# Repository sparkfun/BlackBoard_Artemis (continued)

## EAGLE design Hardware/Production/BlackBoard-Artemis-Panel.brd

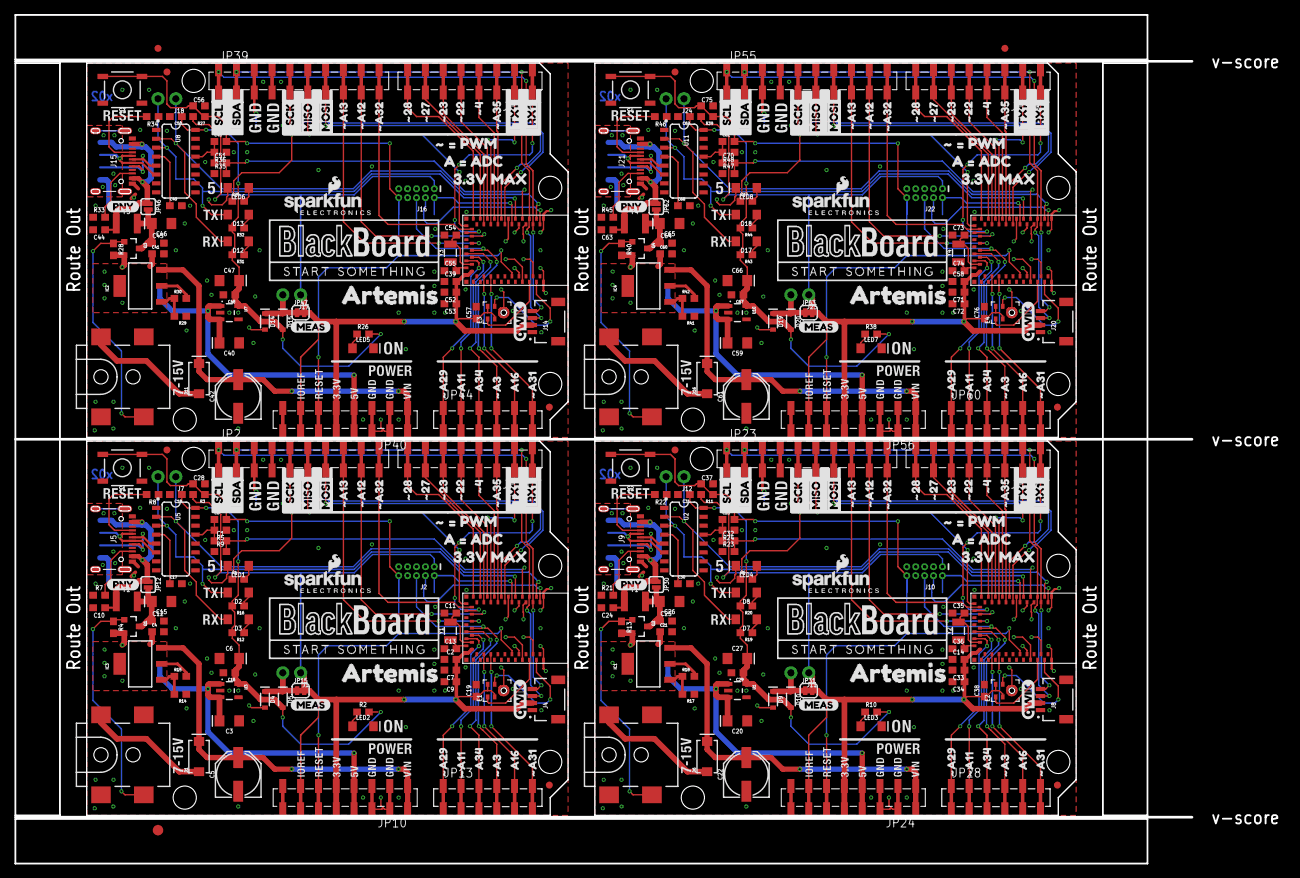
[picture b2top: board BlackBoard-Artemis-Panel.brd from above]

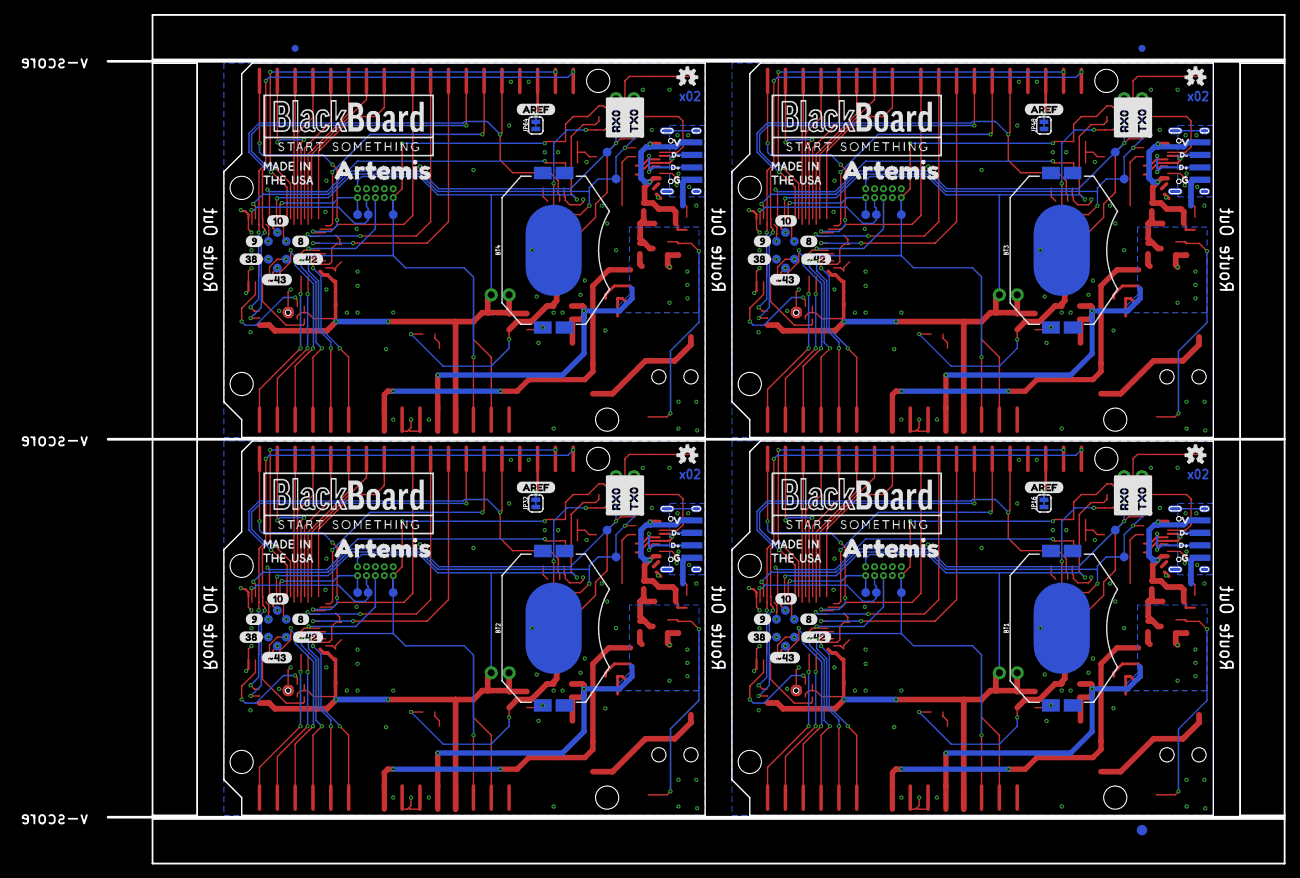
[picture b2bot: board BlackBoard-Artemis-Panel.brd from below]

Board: 2 copper layers, 180.8 x 120.8 mm, 522 parts (131 on the bottom side), 248 nets.

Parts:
BT1, BT2, BT3, BT4: CR2032; BATTCON_20MM_4LEGS_OVERPASTE
C1, C32, C51, C70: 2.2uF; 0603
C2, C4, C8, C10, C12, C14, C18, C19, C21, C23, C24, C25, C31, C38, C39, C41, C43, C44, C45, C50, C57, C58, C60, C62, C63, C64, C69, C76: 0.1uF; 0603
C3, C6, C15, C20, C26, C27, C40, C46, C47, C59, C65, C66: 10uF; EIA3216
C5, C22, C42, C61: 47uF; PANASONIC_D
C7, C33, C52, C71: 10uF; 0603
C9, C16, C29, C34, C48, C53, C67, C72: 1.0uF; 0603
C11, C13, C35, C36, C54, C55, C73, C74: 15pF; 0603
C17, C30, C49, C68: 10nF; 0603
C28, C37, C56, C75: 1nF; 0603
D1, D6, D11, D16: 1A/40V/500mV; SMA-DIODE
D2, D8, D13, D18: GREEN; LED-1206
D3, D7, D12, D17: Yellow; LED-1206
D4, D5, D9, D10, D14, D15, D19, D20: 1A/23V/620mV; SOD-323
E1, E2, E3, E4: SPH0641LM4H-1; SPH0641LM4H-1_MICROPHONE
E$1, E$2, E$3, E$4: FIDUCIAL-1X2
E$5, E$6: FIDUCIAL-1.5X3
F1, F2, F3, F4: 6V/2A; 1210
FRAME1, FRAME2, FRAME3, FRAME4: FRAME-LETTERNO_PACKAGE; DUMMY
IC1, IC2, IC3, IC4: LM1117; SOT223-ALT1
J1, J7, J11, J12, J17, J18, J23, J24: 1X02_NO_SILK
J2, J10, J16, J22: CORTEX_DEBUG; 2X5-PTH-1.27MM-NO_SILK
J3, J6, J13, J19: POWER_JACKTOE; POWER_JACK_SMD_OVERPASTE_TOE
J4, J8, J14, J20: JST04_1MM_RA
J5, J9, J15, J21: USB-C; USB-C-16P
JP1, JP25, JP41, JP57: SFE_LOGO_NAME.1_INCH; SFE_LOGO_NAME_.1
JP2, JP23, JP39, JP55: M10SMD_COMBO; 1X10_SMD_COMBINED
JP3, JP4, JP5, JP6, JP17, JP18, JP19, JP20, JP33, JP34, JP35, JP36, JP49, JP50, JP51, JP52: STAND-OFF
JP7, JP26, JP42, JP58: SFE_LOGO_FLAME.1_INCH; SFE_LOGO_FLAME_.1
JP8, JP9, JP21, JP22, JP37, JP38, JP53, JP54: FIDUCIAL1X2; FIDUCIAL-1X2
JP10, JP24, JP40, JP56: 1X08_SMD_COMBINED
JP11, JP27, JP43, JP59: JP11; 1X08_SMD_COMBINED
JP12, JP30, JP46, JP62: SMT-JUMPER_2_NO_SILK
JP13, JP28, JP44, JP60: 1X06_SMD_STRAIGHT_COMBO
JP14, JP29, JP45, JP61: USB_SOLDER_PADS; USB-SOLDER-PADS
JP15, JP16, JP31, JP32, JP47, JP48, JP63, JP64: SMT-JUMPER_2_NC_TRACE_SILK
LED1, LED4, LED6, LED8: BLUE; LED-1206
LED2, LED3, LED5, LED7: GREEN; LED-1206
Q1, Q2, Q3, Q4: 1.1A/60V/600mΩ; SOT23-3
R1, R6, R12, R16, R19, R20, R25, R31, R32, R37, R43, R44: 4.7k; 0603
R2, R4, R9, R10, R13, R23, R26, R28, R35, R38, R40, R47: 10k; 0603
R3, R5, R11, R24, R27, R36, R39, R48: 100k; 0603
R7, R8, R21, R22, R33, R34, R45, R46: 5.1k; 0603
R14, R17, R29, R41: 715; 0603
R15, R18, R30, R42: 240; 0603
S1, S2, S3, S4: TACTILE_SWITCH_SMD_5.2MM
TP1, TP2, TP3, TP4, TP7, TP8, TP9, TP11, TP12, TP13, TP14, TP16, TP17, TP18, TP19, TP20, TP21, TP22, TP23, TP24, TP27, TP28, TP29, TP30, TP31, TP32, TP33, TP34, TP35, TP38, TP39, TP40, TP41, TP42, TP43, TP44: PAD.03X.05
TP5, TP6, TP10, TP15, TP25, TP26, TP36, TP37: TEST-POINT3X5; PAD.03X.05
U1, U3, U7, U10: AP2112-3.3V; SOT23-5
U2, U5, U8, U11: CH340C; SO016
U4, U6, U9, U12: ARTEMIS_MODULESMD; ARTEMIS_FP
U$1, U$3, U$6, U$7, U$96, U$97, U$143, U$144: BLACKBOARDLOGO#PNG
U$2, U$37, U$102, U$149: D#3
U$4, U$8, U$98, U$145: MADEINUSA#PNG
U$5, U$16, U$95, U$142: OSHW-LOGOS; OSHW-LOGO-S
U$9, U$23, U$99, U$146: QWIIC_COPYRIGHT_SMALL
U$10, U$39, U$103, U$150: D#4
U$11, U$24, U$100, U$147: G1
U$12, U$32, U$101, U$148: V0
U$13, U$40, U$104, U$151: PNY0
U$14, U$15, U$41, U$42, U$105, U$106, U$152, U$153: ARTEMIS0
U$17, U$43, U$107, U$154: A160
U$18, U$93, U$140, U$187: SCL1
U$19, U$44, U$108, U$155: #48
U$20, U$92, U$139, U$186: AREF2
U$21, U$45, U$109, U$156: #229
U$22, U$94, U$141, U$188: SDA0
U$25, U$46, U$110, U$157: #2310
U$26, U$51, U$111, U$158: #2711
U$27, U$52, U$112, U$159: #2812
U$28, U$54, U$113, U$160: #A31
U$29, U$55, U$114, U$161: #A113
U$30, U$56, U$115, U$162: #A294
U$31, U$57, U$116, U$163: #A310
U$33, U$58, U$117, U$164: #A357
U$34, U$59, U$118, U$165: #A1214
U$35, U$68, U$119, U$166: #A1315
U$36, U$73, U$120, U$167: #A3213
U$38, U$74, U$121, U$168: A342
U$47, U$75, U$122, U$169: MISO8
U$48, U$76, U$123, U$170: MOSI7
U$49, U$90, U$137, U$184: RX01
U$50, U$77, U$124, U$171: SCK9
U$53, U$91, U$138, U$185: TX00
U$60, U$78, U$125, U$172: #425
U$61, U$79, U$126, U$173: #434
U$62, U$80, U$127, U$174: 80
U$63, U$81, U$128, U$175: 91
U$64, U$82, U$129, U$176: 102
U$65, U$83, U$130, U$177: 383
U$66, U$84, U$131, U$178: #_#_PWM7
U$67, U$85, U$132, U$179: 3#3V_MAX2
U$69, U$86, U$133, U$180: A_#_ADC6
U$70, U$87, U$134, U$181: MEAS3
U$71, U$88, U$135, U$182: RX11
U$72, U$89, U$136, U$183: TX10
Y1, Y2, Y3, Y4: 32.768kHz; CRYSTAL-SMD-3.2X1.5MM

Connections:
3.3V: C6.+, C16.1, C18.1, D5.A, R2.2, R12.2, R16.2, U3.5, U5.16
3.3V1: C27.+, C29.1, C31.1, D10.A, R10.2, R19.2, R20.2, U1.5, U2.16
3.3V2: C47.+, C48.1, C50.1, D15.A, R26.2, R31.2, R32.2, U7.5, U8.16
3.3V3: C66.+, C67.1, C69.1, D20.A, R38.2, R43.2, R44.2, U10.5, U11.16
5V: C3.+, C4.1, IC3.2, IC3.4, JP10.4A, JP10.4B, Q1.2, R4.2, R15.2, U3.1, U3.3
5V1: C20.+, C21.1, IC1.2, IC1.4, JP24.4A, JP24.4B, Q2.2, R13.2, R18.2, U1.1, U1.3
5V2: C40.+, C41.1, IC2.2, IC2.4, JP40.4A, JP40.4B, Q3.2, R28.2, R30.2, U7.1, U7.3
5V3: C59.+, C60.1, IC4.2, IC4.4, JP56.4A, JP56.4B, Q4.2, R40.2, R42.2, U10.1, U10.3
!DTR: C1.1, C8.1, R5.2, U5.13
!DTR1: C23.1, C32.1, R24.2, U2.13
!DTR2: C43.1, C51.1, R36.2, U8.13
!DTR3: C62.1, C70.1, R48.2, U11.13
!RESET: C8.2, C28.1, J2.10, JP10.6A, JP10.6B, R3.1, S1.3, S1.4, TP3.P$1, U4.~RST
!RESET1: C23.2, C37.1, J10.10, JP24.6A, JP24.6B, R11.1, S2.3, S2.4, TP16.P$1, U6.~RST
!RESET2: C43.2, C56.1, J16.10, JP40.6A, JP40.6B, R27.1, S3.3, S3.4, TP27.P$1, U9.~RST
!RESET3: C62.2, C75.1, J22.10, JP56.6A, JP56.6B, R39.1, S4.3, S4.4, TP38.P$1, U12.~RST
AD1: JP28.5A, JP28.5B, U6.AD16
AD2: JP28.3A, JP28.3B, U6.AD34
AD3: JP44.5A, JP44.5B, U9.AD16
AD4: JP44.3A, JP44.3B, U9.AD34
AD5: JP60.5A, JP60.5B, U12.AD16
AD6: JP60.3A, JP60.3B, U12.AD34
AD16: JP13.5A, JP13.5B, U4.AD16
AD34: JP13.3A, JP13.3B, U4.AD34
BOOT: C1.2, R9.2, U4.BOOT
BOOT1: C32.2, R23.2, U6.BOOT
BOOT2: C51.2, R35.2, U9.BOOT
BOOT3: C70.2, R47.2, U12.BOOT
CC1: J5.A5, R8.2
CC2: J5.B5, R7.2
CC3: J9.B5, R21.2
CC4: J9.A5, R22.2
CC5: J15.B5, R33.2
CC6: J15.A5, R34.2
CC7: J21.B5, R45.2
CC8: J21.A5, R46.2
D1: TP20.P$1, U6.D8
D2: TP21.P$1, U6.D9
D3: TP22.P$1, U6.D10
D4: TP19.P$1, U6.D38
D5: TP31.P$1, U9.D8
D6: TP32.P$1, U9.D9
D7: TP33.P$1, U9.D10
D7/MOSI: JP2.7A, JP2.7B, U4.D7
D7/MOSI1: JP23.7A, JP23.7B, U6.D7
D7/MOSI2: JP39.7A, JP39.7B, U9.D7
D7/MOSI3: JP55.7A, JP55.7B, U12.D7
D8: TP12.P$1, U4.D8
D9: TP13.P$1, U4.D9
D10: TP14.P$1, U4.D10
D11: TP30.P$1, U9.D38
D12: TP42.P$1, U12.D8
D13: TP43.P$1, U12.D9
D14: TP44.P$1, U12.D10
D15: TP41.P$1, U12.D38
D38: TP11.P$1, U4.D38
D40/SDA: J4.3, JP2.2A, JP2.2B, U4.D40
D40/SDA1: J8.3, JP23.2A, JP23.2B, U6.D40
D40/SDA2: J14.3, JP39.2A, JP39.2B, U9.D40
D40/SDA3: J20.3, JP55.2A, JP55.2B, U12.D40
D+: J5.A6, J5.B6, JP14.D+, U5.5
D+1: J9.A6, J9.B6, JP29.D+, U2.5
D+2: J15.A6, J15.B6, JP45.D+, U8.5
D+3: J21.A6, J21.B6, JP61.D+, U11.5
D-: J5.A7, J5.B7, JP14.D-, U5.6
D-1: J9.A7, J9.B7, JP29.D-, U2.6
D-2: J15.A7, J15.B7, JP45.D-, U8.6
D-3: J21.A7, J21.B7, JP61.D-, U11.6
GND: BT1.2, C2.1, C3.-, C4.2, C5.-, C6.-, C7.2, C9.2, C10.2, C11.1, C12.2, C13.1, C15.-, C16.2, C17.2, C18.2, C19.2, C28.2, E1.3, E1.6, E1.7, E1.8, J2.3, J2.5, J2.9, J3.GND, J4.1, J5.GND, J5.GND2, JP2.4A, JP2.4B, JP10.2A, JP10.2B, JP10.3A, JP10.3B, JP14.GND, JP16.1, LED1.C, LED2.C, R5.1, R7.1, R8.1, R9.1, R14.1, S1.1, S1.2, U3.2, U4.GND@1, U4.GND@22, U4.GND@38, U4.GND@39, U4.GND@47, U4.GND@59, U5.1
GND1: BT2.2, C14.1, C20.-, C21.2, C22.-, C24.2, C25.2, C26.-, C27.-, C29.2, C30.2, C31.2, C33.2, C34.2, C35.1, C36.1, C37.2, C38.2, E2.3, E2.6, E2.7, E2.8, J6.GND, J8.1, J9.GND, J9.GND2, J10.3, J10.5, J10.9, JP23.4A, JP23.4B, JP24.2A, JP24.2B, JP24.3A, JP24.3B, JP29.GND, JP32.1, LED3.C, LED4.C, R17.1, R21.1, R22.1, R23.1, R24.1, S2.1, S2.2, U1.2, U2.1, U6.GND@1, U6.GND@22, U6.GND@38, U6.GND@39, U6.GND@47, U6.GND@59
GND2: BT3.2, C39.1, C40.-, C41.2, C42.-, C44.2, C45.2, C46.-, C47.-, C48.2, C49.2, C50.2, C52.2, C53.2, C54.1, C55.1, C56.2, C57.2, E3.3, E3.6, E3.7, E3.8, J13.GND, J14.1, J15.GND, J15.GND2, J16.3, J16.5, J16.9, JP39.4A, JP39.4B, JP40.2A, JP40.2B, JP40.3A, JP40.3B, JP45.GND, JP48.1, LED5.C, LED6.C, R29.1, R33.1, R34.1, R35.1, R36.1, S3.1, S3.2, U7.2, U8.1, U9.GND@1, U9.GND@22, U9.GND@38, U9.GND@39, U9.GND@47, U9.GND@59
GND3: BT4.2, C58.1, C59.-, C60.2, C61.-, C63.2, C64.2, C65.-, C66.-, C67.2, C68.2, C69.2, C71.2, C72.2, C73.1, C74.1, C75.2, C76.2, E4.3, E4.6, E4.7, E4.8, J19.GND, J20.1, J21.GND, J21.GND2, J22.3, J22.5, J22.9, JP55.4A, JP55.4B, JP56.2A, JP56.2B, JP56.3A, JP56.3B, JP61.GND, JP64.1, LED7.C, LED8.C, R41.1, R45.1, R46.1, R47.1, R48.1, S4.1, S4.2, U10.2, U11.1, U12.GND@1, U12.GND@22, U12.GND@38, U12.GND@39, U12.GND@47, U12.GND@59
INSERT: J3.P$4, Q1.1, R4.1
INSERT1: J6.P$4, Q2.1, R13.1
INSERT2: J13.P$4, Q3.1, R28.1
INSERT3: J19.P$4, Q4.1, R40.1
unnamed: LED1.A, R1.2
unnamed: LED2.A, R2.1
unnamed: D4.C, D5.C, J1.2, JP15.1
unnamed: D2.A, R16.1
unnamed: C17.1, U5.4
unnamed: C11.2, U4.XO, Y1.P$2
unnamed: C13.2, U4.XI, Y1.P$1
unnamed: D3.A, R12.1
unnamed: JP2.3A, JP2.3B, JP16.2
unnamed: LED3.A, R10.1
unnamed: LED4.A, R6.2
unnamed: IC1.1, R17.2, R18.1
unnamed: D8.A, R20.1
unnamed: IC3.1, R14.2, R15.1
unnamed: D7.A, R19.1
unnamed: C30.1, U2.4
unnamed: D9.C, D10.C, J11.2, JP31.1
unnamed: C35.2, U6.XO, Y2.P$2
unnamed: C36.2, U6.XI, Y2.P$1
unnamed: JP23.3A, JP23.3B, JP32.2
unnamed: LED5.A, R26.1
unnamed: LED6.A, R25.2
unnamed: IC2.1, R29.2, R30.1
unnamed: D13.A, R32.1
unnamed: D12.A, R31.1
unnamed: C49.1, U8.4
unnamed: D14.C, D15.C, J17.2, JP47.1
unnamed: C54.2, U9.XO, Y3.P$2
unnamed: C55.2, U9.XI, Y3.P$1
unnamed: JP39.3A, JP39.3B, JP48.2
unnamed: LED7.A, R38.1
unnamed: LED8.A, R37.2
unnamed: IC4.1, R41.2, R42.1
unnamed: D18.A, R44.1
unnamed: D17.A, R43.1
unnamed: C68.1, U11.4
unnamed: D19.C, D20.C, J23.2, JP63.1
unnamed: C73.2, U12.XO, Y4.P$2
unnamed: C74.2, U12.XI, Y4.P$1
unnamed: JP55.3A, JP55.3B, JP64.2
PDMCLK: E1.4, U4.~D37
PDMCLK1: E2.4, U6.~D37
PDMCLK2: E3.4, U9.~D37
PDMCLK3: E4.4, U12.~D37
PDMDATA: E1.1, U4.D36
PDMDATA1: E2.1, U6.D36
PDMDATA2: E3.1, U9.D36
PDMDATA3: E4.1, U12.D36
PWRIN: D1.A, J3.VIN0
PWRIN1: D6.A, J6.VIN0
PWRIN2: D11.A, J13.VIN0
PWRIN3: D16.A, J19.VIN0
RXI-0: D3.C, J7.1, TP5.P$1, U4.RXI-0, U5.2
RXI-1: D7.C, J12.1, TP10.P$1, U2.2, U6.RXI-0
RXI-2: D12.C, J18.1, TP25.P$1, U8.2, U9.RXI-0
RXI-3: D17.C, J24.1, TP36.P$1, U11.2, U12.RXI-0
SHLD: J5.SHLD1, J5.SHLD2, J5.SHLD3, J5.SHLD4, J5.SHLD5, J5.SHLD6, J5.SHLD7, J5.SHLD8
SHLD1: J9.SHLD1, J9.SHLD2, J9.SHLD3, J9.SHLD4, J9.SHLD5, J9.SHLD6, J9.SHLD7, J9.SHLD8
SHLD2: J15.SHLD1, J15.SHLD2, J15.SHLD3, J15.SHLD4, J15.SHLD5, J15.SHLD6, J15.SHLD7, J15.SHLD8
SHLD3: J21.SHLD1, J21.SHLD2, J21.SHLD3, J21.SHLD4, J21.SHLD5, J21.SHLD6, J21.SHLD7, J21.SHLD8
SWDCK: J2.4, TP1.P$1, U4.SWDCK
SWDCK1: J10.4, TP4.P$1, U6.SWDCK
SWDCK2: J16.4, TP23.P$1, U9.SWDCK
SWDCK3: J22.4, TP34.P$1, U12.SWDCK
SWDIO: J2.2, TP2.P$1, U4.SWDIO
SWDIO1: J10.2, TP7.P$1, U6.SWDIO
SWDIO2: J16.2, TP24.P$1, U9.SWDIO
SWDIO3: J22.2, TP35.P$1, U12.SWDIO
TXO-0: D2.C, J7.2, TP6.P$1, U4.TXO-0, U5.3
TXO-1: D8.C, J12.2, TP15.P$1, U2.3, U6.TXO-0
TXO-2: D13.C, J18.2, TP26.P$1, U8.3, U9.TXO-0
TXO-3: D18.C, J24.2, TP37.P$1, U11.3, U12.TXO-0
USBVCC: C12.1, C15.+, F2.2, JP12.2, Q1.3
USBVCC1: C25.1, C26.+, F1.2, JP30.2, Q2.3
USBVCC2: C45.1, C46.+, F3.2, JP46.2, Q3.3
USBVCC3: C64.1, C65.+, F4.2, JP62.2, Q4.3
VDD: C2.2, C7.1, C9.1, C19.1, E1.2, E1.5, J1.1, J2.1, J4.2, JP10.5A, JP10.5B, JP10.7A, JP10.7B, JP15.2, R3.2, U4.VDD@36, U4.VDD@37
VDD1: C14.2, C33.1, C34.1, C38.1, E2.2, E2.5, J8.2, J10.1, J11.1, JP24.5A, JP24.5B, JP24.7A, JP24.7B, JP31.2, R11.2, U6.VDD@36, U6.VDD@37
VDD2: C39.2, C52.1, C53.1, C57.1, E3.2, E3.5, J14.2, J16.1, J17.1, JP40.5A, JP40.5B, JP40.7A, JP40.7B, JP47.2, R27.2, U9.VDD@36, U9.VDD@37
VDD3: C58.2, C71.1, C72.1, C76.1, E4.2, E4.5, J20.2, J22.1, J23.1, JP56.5A, JP56.5B, JP56.7A, JP56.7B, JP63.2, R39.2, U12.VDD@36, U12.VDD@37
VIN: C5.+, D1.C, IC3.3, JP10.1A, JP10.1B
VIN1: C22.+, D6.C, IC1.3, JP24.1A, JP24.1B
VIN2: C42.+, D11.C, IC2.3, JP40.1A, JP40.1B
VIN3: C61.+, D16.C, IC4.3, JP56.1A, JP56.1B
VUSB: C10.1, F2.1, J5.VBUS1, J5.VBUS2, JP12.1, JP14.VBUS
VUSB1: C24.1, F1.1, J9.VBUS1, J9.VBUS2, JP29.VBUS, JP30.1
VUSB2: C44.1, F3.1, J15.VBUS1, J15.VBUS2, JP45.VBUS, JP46.1
VUSB3: C63.1, F4.1, J21.VBUS1, J21.VBUS2, JP61.VBUS, JP62.1
V_BATT: BT1.1, D4.A
V_BATT1: BT2.1, D9.A
V_BATT2: BT3.1, D14.A
V_BATT3: BT4.1, D19.A
~AD1: JP28.6A, JP28.6B, U6.~AD31
~AD2: JP28.1A, JP28.1B, U6.~AD29
~AD3: JP28.2A, JP28.2B, U6.~AD11
~AD3/SWO: J2.6, JP13.4A, JP13.4B, U4.~AD33/SWO
~AD3/SWO1: J10.6, JP28.4A, JP28.4B, U6.~AD33/SWO
~AD3/SWO2: J16.6, JP44.4A, JP44.4B, U9.~AD33/SWO
~AD3/SWO3: J22.6, JP60.4A, JP60.4B, U12.~AD33/SWO
~AD4: JP27.3A, JP27.3B, U6.~AD35
~AD5: JP23.10A, JP23.10B, U6.~AD32
~AD6: JP23.9A, JP23.9B, U6.~AD12
~AD7: JP23.8A, JP23.8B, U6.~AD13
~AD8: JP44.6A, JP44.6B, U9.~AD31
~AD9: JP44.1A, JP44.1B, U9.~AD29
~AD10: JP44.2A, JP44.2B, U9.~AD11
~AD11: JP13.2A, JP13.2B, U4.~AD11
~AD12: JP2.9A, JP2.9B, U4.~AD12
~AD13: JP2.8A, JP2.8B, U4.~AD13
~AD14: JP43.3A, JP43.3B, U9.~AD35
~AD15: JP39.10A, JP39.10B, U9.~AD32
~AD16: JP39.9A, JP39.9B, U9.~AD12
~AD17: JP39.8A, JP39.8B, U9.~AD13
~AD18: JP60.6A, JP60.6B, U12.~AD31
~AD19: JP60.1A, JP60.1B, U12.~AD29
~AD20: JP60.2A, JP60.2B, U12.~AD11
~AD21: JP59.3A, JP59.3B, U12.~AD35
~AD22: JP55.10A, JP55.10B, U12.~AD32
~AD23: JP55.9A, JP55.9B, U12.~AD12
~AD24: JP55.8A, JP55.8B, U12.~AD13
~AD29: JP13.1A, JP13.1B, U4.~AD29
~AD31: JP13.6A, JP13.6B, U4.~AD31
~AD32: JP2.10A, JP2.10B, U4.~AD32
~AD35: JP11.3A, JP11.3B, U4.~AD35
~D1: JP27.4A, JP27.4B, U6.~D4
~D2: JP27.5A, JP27.5B, U6.~D22
~D3: JP27.6A, JP27.6B, U6.~D23
~D4: JP11.4A, JP11.4B, U4.~D4
~D5: JP27.7A, JP27.7B, U6.~D27
~D5/SCK: JP2.5A, JP2.5B, R1.1, U4.~D5
~D5/SCK1: JP23.5A, JP23.5B, R6.1, U6.~D5
~D5/SCK2: JP39.5A, JP39.5B, R25.1, U9.~D5
~D5/SCK3: JP55.5A, JP55.5B, R37.1, U12.~D5
~D6: JP27.8A, JP27.8B, U6.~D28
~D6/MISO: JP2.6A, JP2.6B, U4.~D6
~D6/MISO1: JP23.6A, JP23.6B, U6.~D6
~D6/MISO2: JP39.6A, JP39.6B, U9.~D6
~D6/MISO3: JP55.6A, JP55.6B, U12.~D6
~D7: TP18.P$1, U6.~D42
~D8: TP17.P$1, U6.~D43
~D9: JP43.4A, JP43.4B, U9.~D4
~D10: JP43.5A, JP43.5B, U9.~D22
~D11: JP43.6A, JP43.6B, U9.~D23
~D12: JP43.7A, JP43.7B, U9.~D27
~D13: JP43.8A, JP43.8B, U9.~D28
~D14: TP29.P$1, U9.~D42
~D15: TP28.P$1, U9.~D43
~D16: JP59.4A, JP59.4B, U12.~D4
~D17: JP59.5A, JP59.5B, U12.~D22
~D18: JP59.6A, JP59.6B, U12.~D23
~D19: JP59.7A, JP59.7B, U12.~D27
~D20: JP59.8A, JP59.8B, U12.~D28
~D21: TP40.P$1, U12.~D42
~D22: JP11.5A, JP11.5B, U4.~D22
~D23: JP11.6A, JP11.6B, U4.~D23
~D24: TP39.P$1, U12.~D43
~D24/TXO-1: JP11.2A, JP11.2B, U4.~D24
~D24/TXO-2: JP27.2A, JP27.2B, U6.~D24
~D24/TXO-3: JP43.2A, JP43.2B, U9.~D24
~D24/TXO-4: JP59.2A, JP59.2B, U12.~D24
~D25/RXI-1: JP11.1A, JP11.1B, U4.~D25
~D25/RXI-2: JP27.1A, JP27.1B, U6.~D25
~D25/RXI-3: JP43.1A, JP43.1B, U9.~D25
~D25/RXI-4: JP59.1A, JP59.1B, U12.~D25
~D27: JP11.7A, JP11.7B, U4.~D27
~D28: JP11.8A, JP11.8B, U4.~D28
~D39/SCL: J4.4, JP2.1A, JP2.1B, U4.~D39
~D39/SCL1: J8.4, JP23.1A, JP23.1B, U6.~D39
~D39/SCL2: J14.4, JP39.1A, JP39.1B, U9.~D39
~D39/SCL3: J20.4, JP55.1A, JP55.1B, U12.~D39
~D42: TP9.P$1, U4.~D42
~D43: TP8.P$1, U4.~D43

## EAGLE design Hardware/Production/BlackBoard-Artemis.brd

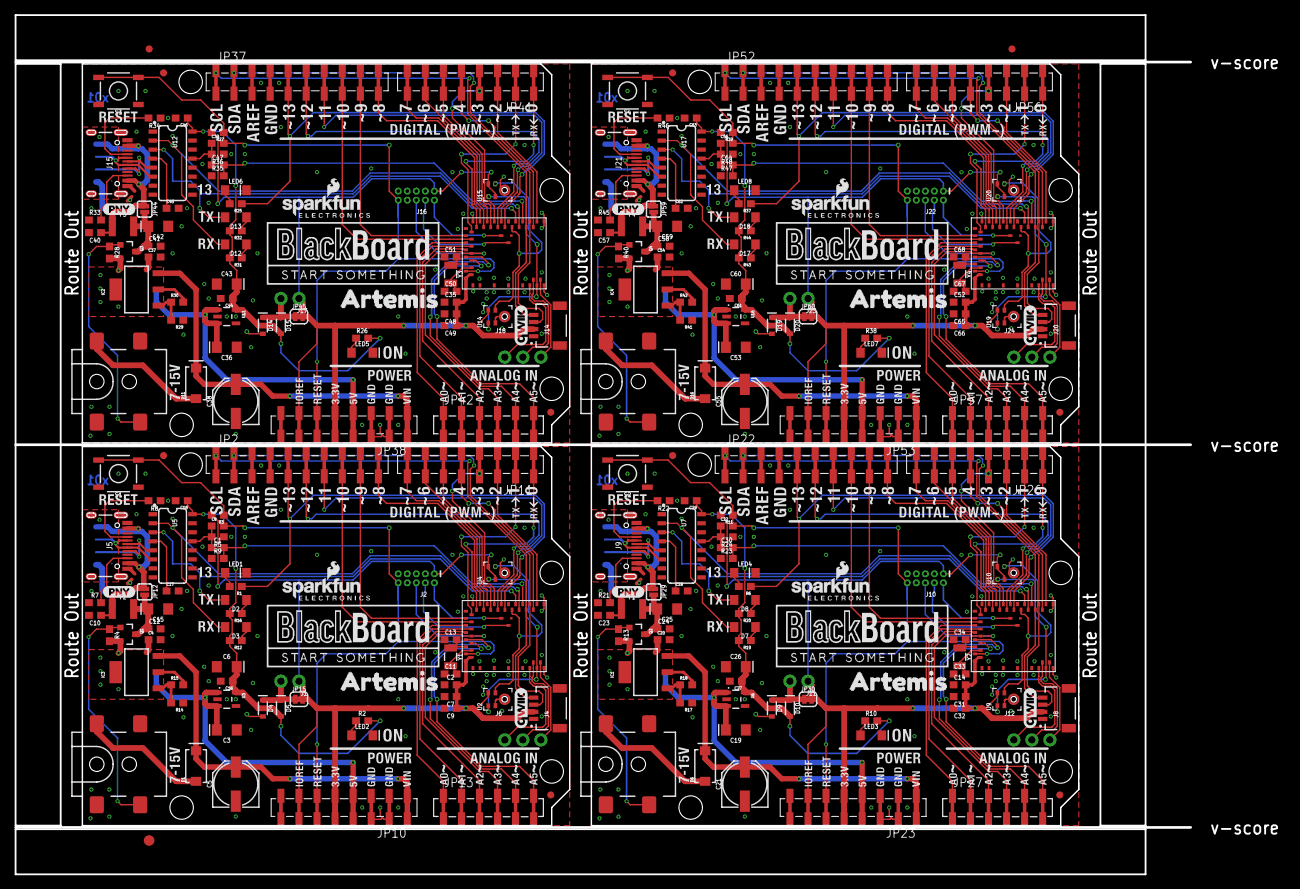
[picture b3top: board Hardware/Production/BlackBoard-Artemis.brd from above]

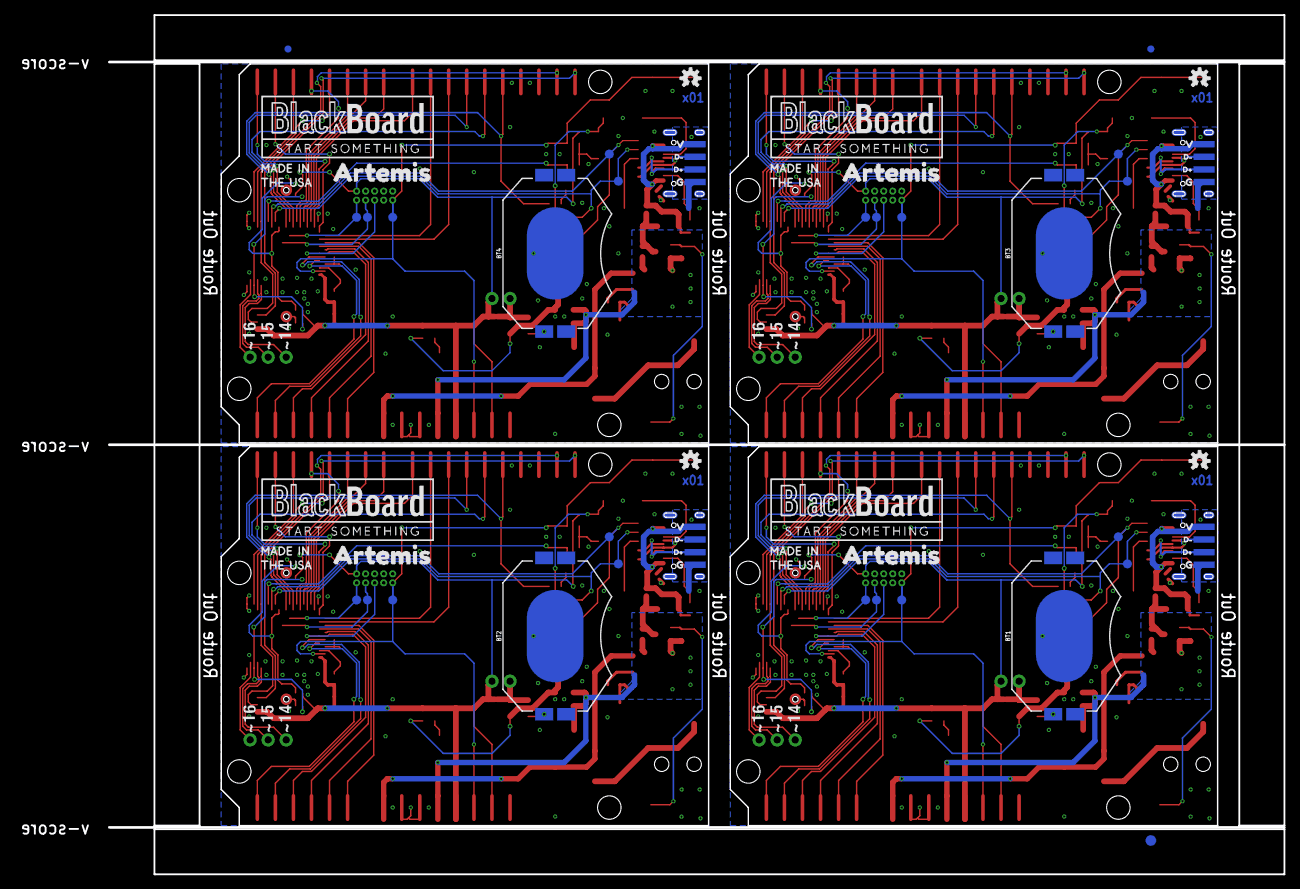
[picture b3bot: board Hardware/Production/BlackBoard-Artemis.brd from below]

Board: 2 copper layers, 178.5 x 120.8 mm, 354 parts (63 on the bottom side), 232 nets.

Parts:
BT1, BT2, BT3, BT4: CR2032; BATTCON_20MM_4LEGS_OVERPASTE
C1, C30, C47, C64: 2.2uF; 0603
C2, C4, C10, C12, C14, C18, C20, C23, C24, C29, C35, C37, C40, C41, C46, C52, C54, C57, C58, C63: 0.1uF; 0603
C3, C6, C15, C19, C25, C26, C36, C42, C43, C53, C59, C60: 10uF; EIA3216
C5, C21, C38, C55: 47uF; PANASONIC_D
C7, C31, C48, C65: 10uF; 0603
C8, C17, C22, C28, C39, C45, C56, C62: 10nF; 0603
C9, C16, C27, C32, C44, C49, C61, C66: 1.0uF; 0603
C11, C13, C33, C34, C50, C51, C67, C68: 15pF; 0603
D1, D6, D11, D16: 1A/40V/500mV; SMA-DIODE
D2, D8, D13, D18: GREEN; LED-1206
D3, D7, D12, D17: Yellow; LED-1206
D4, D5, D9, D10, D14, D15, D19, D20: 1A/23V/620mV; SOD-323
E$1, E$2, E$3, E$4: FIDUCIAL-1X2
E$5, E$6: FIDUCIAL-1.5X3
F1, F2, F3, F4: 6V/2A; 1210
FRAME1, FRAME3, FRAME5, FRAME7: FRAME-LETTER; CREATIVE_COMMONS
FRAME2, FRAME4, FRAME6, FRAME8: FRAME-LETTERNO_PACKAGE; DUMMY
IC1, IC2, IC3, IC4: LM1117; SOT223-ALT1
J1, J11, J17, J23: 1X02_NO_SILK
J2, J10, J16, J22: CORTEX_DEBUG; 2X5-PTH-1.27MM-NO_SILK
J3, J7, J13, J19: POWER_JACKSUPER_BOMB_DIGITY; POWER_JACK_SMD_OVERPASTE_SUPER_BOMB_DIGITY
J4, J8, J14, J20: JST04_1MM_RA
J5, J9, J15, J21: USB C; USB-C-16P
J6, J12, J18, J24: 1X03_NO_SILK
JP1, JP24, JP39, JP54: SFE_LOGO_NAME.1_INCH; SFE_LOGO_NAME_.1
JP2, JP22, JP37, JP52: M10SMD_COMBO; 1X10_SMD_COMBINED
JP3, JP4, JP5, JP6, JP16, JP17, JP18, JP19, JP31, JP32, JP33, JP34, JP46, JP47, JP48, JP49: STAND-OFF
JP7, JP25, JP40, JP55: SFE_LOGO_FLAME.1_INCH; SFE_LOGO_FLAME_.1
JP8, JP9, JP20, JP21, JP35, JP36, JP50, JP51: FIDUCIAL1X2; FIDUCIAL-1X2
JP10, JP23, JP38, JP53: 1X08_SMD_COMBINED
JP11, JP26, JP41, JP56: JP11; 1X08_SMD_COMBINED
JP12, JP29, JP44, JP59: JUMPER-SMT_2_NO_SILK; SMT-JUMPER_2_NO_SILK
JP13, JP27, JP42, JP57: 1X06_SMD_STRAIGHT_COMBO
JP14, JP28, JP43, JP58: USB_SOLDER_PADS; USB-SOLDER-PADS
JP15, JP30, JP45, JP60: SMT-JUMPER_2_NC_TRACE_SILK
LED1, LED4, LED6, LED8: Blue; LED-1206-HIDDENSILK
LED2, LED3, LED5, LED7: GREEN; LED-1206
Q1, Q2, Q3, Q4: 1.1A/60V/600mΩ; SOT23-3
R1, R6, R12, R16, R19, R20, R25, R31, R32, R37, R43, R44: 4.7k; 0603
R2, R4, R9, R10, R13, R23, R26, R28, R35, R38, R40, R47: 10k; 0603
R3, R5, R11, R24, R27, R36, R39, R48: 100k; 0603
R7, R8, R21, R22, R33, R34, R45, R46: 5.1k; 0603
R14, R17, R29, R41: 715; 0603
R15, R18, R30, R42: 240; 0603
S1, S2, S3, S4: TACTILE_SWITCH_SMD_5.2MM
TP1, TP2, TP3, TP4, TP7, TP10, TP11, TP12, TP15, TP16, TP17, TP20: PAD.03X.05
TP5, TP6, TP8, TP9, TP13, TP14, TP18, TP19: TEST-POINT3X5; PAD.03X.05
U1, U8, U13, U18: ARTEMIS_FULL; ARTEMIS
U2, U4, U9, U10, U14, U15, U19, U20: SPH0641LM4H-1; SPH0641LM4H-1_MICROPHONE
U3, U6, U11, U16: AP2112-3.3V; SOT23-5
U5, U7, U12, U17: CH340C; SO016
U$1, U$3, U$6, U$7, U$26, U$27, U$38, U$39: BLACKBOARDLOGO#PNG
U$2, U$20, U$32, U$44: D#3
U$4, U$8, U$28, U$40: MADEINUSA#PNG
U$5, U$16, U$25, U$37: OSHW-LOGOS; OSHW-LOGO-S
U$9, U$17, U$29, U$41: QWIIC_COPYRIGHT_SMALL
U$10, U$21, U$33, U$45: D#4
U$11, U$18, U$30, U$42: G1
U$12, U$19, U$31, U$43: V0
U$13, U$22, U$34, U$46: PNY0
U$14, U$15, U$23, U$24, U$35, U$36, U$47, U$48: ARTEMIS0
Y1, Y2, Y3, Y4: 32.768kHz; CRYSTAL-SMD-3.2X1.5MM

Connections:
3.3V: C6.+, C16.1, C18.1, D5.A, R2.2, R12.2, R16.2, U3.5, U5.16
3.3V1: C26.+, C27.1, C29.1, D10.A, R10.2, R19.2, R20.2, U6.5, U7.16
3.3V2: C43.+, C44.1, C46.1, D15.A, R26.2, R31.2, R32.2, U11.5, U12.16
3.3V3: C60.+, C61.1, C63.1, D20.A, R38.2, R43.2, R44.2, U16.5, U17.16
5V: C3.+, C4.1, IC3.2, IC3.4, JP10.4A, JP10.4B, Q1.2, R4.2, R15.2, U3.1, U3.3
5V1: C19.+, C20.1, IC1.2, IC1.4, JP23.4A, JP23.4B, Q2.2, R13.2, R18.2, U6.1, U6.3
5V2: C36.+, C37.1, IC2.2, IC2.4, JP38.4A, JP38.4B, Q3.2, R28.2, R30.2, U11.1, U11.3
5V3: C53.+, C54.1, IC4.2, IC4.4, JP53.4A, JP53.4B, Q4.2, R40.2, R42.2, U16.1, U16.3
!DTR: C1.1, C8.1, R5.2, U5.13
!DTR1: C22.1, C30.1, R24.2, U7.13
!DTR2: C39.1, C47.1, R36.2, U12.13
!DTR3: C56.1, C64.1, R48.2, U17.13
!RESET: C8.2, J2.10, JP10.6A, JP10.6B, R3.1, S1.3, S1.4, TP3.P$1, U1.33
!RESET1: C22.2, J10.10, JP23.6A, JP23.6B, R11.1, S2.3, S2.4, TP10.P$1, U8.33
!RESET2: C39.2, J16.10, JP38.6A, JP38.6B, R27.1, S3.3, S3.4, TP15.P$1, U13.33
!RESET3: C56.2, J22.10, JP53.6A, JP53.6B, R39.1, S4.3, S4.4, TP20.P$1, U18.33
BOOT: C1.2, R9.2, U1.6
BOOT1: C30.2, R23.2, U8.6
BOOT2: C47.2, R35.2, U13.6
BOOT3: C64.2, R47.2, U18.6
CC1: J5.A5, R8.2
CC2: J5.B5, R7.2
CC3: J9.B5, R21.2
CC4: J9.A5, R22.2
CC5: J15.B5, R33.2
CC6: J15.A5, R34.2
CC7: J21.B5, R45.2
CC8: J21.A5, R46.2
D1: JP26.5A, JP26.5B, U8.3
D2: JP41.5A, JP41.5B, U13.3
D3: JP56.5A, JP56.5B, U18.3
D4: JP11.5A, JP11.5B, U1.3
D11/MOSI: JP2.7A, JP2.7B, U1.12
D11/MOSI1: JP22.7A, JP22.7B, U8.12
D11/MOSI2: JP37.7A, JP37.7B, U13.12
D11/MOSI3: JP52.7A, JP52.7B, U18.12
D+: J5.A6, J5.B6, JP14.D+, U5.5
D+1: J9.A6, J9.B6, JP28.D+, U7.5
D+2: J15.A6, J15.B6, JP43.D+, U12.5
D+3: J21.A6, J21.B6, JP58.D+, U17.5
D-: J5.A7, J5.B7, JP14.D-, U5.6
D-1: J9.A7, J9.B7, JP28.D-, U7.6
D-2: J15.A7, J15.B7, JP43.D-, U12.6
D-3: J21.A7, J21.B7, JP58.D-, U17.6
GND: BT1.2, C2.1, C3.-, C4.2, C5.-, C6.-, C7.2, C9.2, C10.2, C11.1, C12.2, C13.1, C15.-, C16.2, C17.2, C18.2, J2.3, J2.5, J2.9, J3.GND, J4.1, J5.GND, J5.GND2, JP2.4A, JP2.4B, JP10.2A, JP10.2B, JP10.3A, JP10.3B, JP14.GND, LED1.C, LED2.C, R5.1, R7.1, R8.1, R9.1, R14.1, S1.1, S1.2, U1.1, U1.20, U1.21, U1.36, U1.37, U1.38, U1.39, U1.40, U1.45, U2.2, U2.3, U3.2, U4.3, U5.1
GND1: BT2.2, C14.1, C19.-, C20.2, C21.-, C23.2, C24.2, C25.-, C26.-, C27.2, C28.2, C29.2, C31.2, C32.2, C33.1, C34.1, J7.GND, J8.1, J9.GND, J9.GND2, J10.3, J10.5, J10.9, JP22.4A, JP22.4B, JP23.2A, JP23.2B, JP23.3A, JP23.3B, JP28.GND, LED3.C, LED4.C, R17.1, R21.1, R22.1, R23.1, R24.1, S2.1, S2.2, U6.2, U7.1, U8.1, U8.20, U8.21, U8.36, U8.37, U8.38, U8.39, U8.40, U8.45, U9.2, U9.3, U10.3
GND2: BT3.2, C35.1, C36.-, C37.2, C38.-, C40.2, C41.2, C42.-, C43.-, C44.2, C45.2, C46.2, C48.2, C49.2, C50.1, C51.1, J13.GND, J14.1, J15.GND, J15.GND2, J16.3, J16.5, J16.9, JP37.4A, JP37.4B, JP38.2A, JP38.2B, JP38.3A, JP38.3B, JP43.GND, LED5.C, LED6.C, R29.1, R33.1, R34.1, R35.1, R36.1, S3.1, S3.2, U11.2, U12.1, U13.1, U13.20, U13.21, U13.36, U13.37, U13.38, U13.39, U13.40, U13.45, U14.2, U14.3, U15.3
GND3: BT4.2, C52.1, C53.-, C54.2, C55.-, C57.2, C58.2, C59.-, C60.-, C61.2, C62.2, C63.2, C65.2, C66.2, C67.1, C68.1, J19.GND, J20.1, J21.GND, J21.GND2, J22.3, J22.5, J22.9, JP52.4A, JP52.4B, JP53.2A, JP53.2B, JP53.3A, JP53.3B, JP58.GND, LED7.C, LED8.C, R41.1, R45.1, R46.1, R47.1, R48.1, S4.1, S4.2, U16.2, U17.1, U18.1, U18.20, U18.21, U18.36, U18.37, U18.38, U18.39, U18.40, U18.45, U19.2, U19.3, U20.3
INSERT: J3.P$4, Q1.1, R4.1
INSERT1: J7.P$4, Q2.1, R13.1
INSERT2: J13.P$4, Q3.1, R28.1
INSERT3: J19.P$4, Q4.1, R40.1
unnamed: LED1.A, R1.2
unnamed: LED2.A, R2.1
unnamed: D4.C, D5.C, J1.2, JP15.1
unnamed: D2.A, R16.1
unnamed: C17.1, U5.4
unnamed: C11.2, U1.32, Y1.P$2
unnamed: C13.2, U1.31, Y1.P$1
unnamed: D3.A, R12.1
unnamed: LED3.A, R10.1
unnamed: LED4.A, R6.2
unnamed: IC1.1, R17.2, R18.1
unnamed: D8.A, R20.1
unnamed: D7.A, R19.1
unnamed: IC3.1, R14.2, R15.1
unnamed: C28.1, U7.4
unnamed: D9.C, D10.C, J11.2, JP30.1
unnamed: C33.2, U8.32, Y2.P$2
unnamed: C34.2, U8.31, Y2.P$1
unnamed: LED5.A, R26.1
unnamed: LED6.A, R25.2
unnamed: IC2.1, R29.2, R30.1
unnamed: D13.A, R32.1
unnamed: D12.A, R31.1
unnamed: C45.1, U12.4
unnamed: D14.C, D15.C, J17.2, JP45.1
unnamed: C50.2, U13.32, Y3.P$2
unnamed: C51.2, U13.31, Y3.P$1
unnamed: LED7.A, R38.1
unnamed: LED8.A, R37.2
unnamed: IC4.1, R41.2, R42.1
unnamed: D18.A, R44.1
unnamed: D17.A, R43.1
unnamed: C62.1, U17.4
unnamed: D19.C, D20.C, J23.2, JP60.1
unnamed: C67.2, U18.32, Y4.P$2
unnamed: C68.2, U18.31, Y4.P$1
PDMCLK: U1.9, U2.4, U4.4
PDMCLK1: U8.9, U9.4, U10.4
PDMCLK2: U13.9, U14.4, U15.4
PDMCLK3: U18.9, U19.4, U20.4
PDMDATA: U1.43, U2.1, U4.1
PDMDATA1: U8.43, U9.1, U10.1
PDMDATA2: U13.43, U14.1, U15.1
PDMDATA3: U18.43, U19.1, U20.1
PWRIN: D1.A, J3.VIN0
PWRIN1: D6.A, J7.VIN0
PWRIN2: D11.A, J13.VIN0
PWRIN3: D16.A, J19.VIN0
RXI-0: D3.C, TP5.P$1, U1.7, U5.2
RXI-1: D7.C, TP8.P$1, U7.2, U8.7
RXI-2: D12.C, TP13.P$1, U12.2, U13.7
RXI-3: D17.C, TP18.P$1, U17.2, U18.7
SDA: J4.3, JP2.2A, JP2.2B, U1.4
SDA1: J8.3, JP22.2A, JP22.2B, U8.4
SDA2: J14.3, JP37.2A, JP37.2B, U13.4
SDA3: J20.3, JP52.2A, JP52.2B, U18.4
SHLD: J5.SHLD1, J5.SHLD2, J5.SHLD3, J5.SHLD4, J5.SHLD5, J5.SHLD6, J5.SHLD7, J5.SHLD8
SHLD1: J9.SHLD1, J9.SHLD2, J9.SHLD3, J9.SHLD4, J9.SHLD5, J9.SHLD6, J9.SHLD7, J9.SHLD8
SHLD2: J15.SHLD1, J15.SHLD2, J15.SHLD3, J15.SHLD4, J15.SHLD5, J15.SHLD6, J15.SHLD7, J15.SHLD8
SHLD3: J21.SHLD1, J21.SHLD2, J21.SHLD3, J21.SHLD4, J21.SHLD5, J21.SHLD6, J21.SHLD7, J21.SHLD8
SWDCK: J2.4, TP1.P$1, U1.47
SWDCK1: J10.4, TP4.P$1, U8.47
SWDCK2: J16.4, TP11.P$1, U13.47
SWDCK3: J22.4, TP16.P$1, U18.47
SWDIO: J2.2, TP2.P$1, U1.46
SWDIO1: J10.2, TP7.P$1, U8.46
SWDIO2: J16.2, TP12.P$1, U13.46
SWDIO3: J22.2, TP17.P$1, U18.46
TXO-0: D2.C, TP6.P$1, U1.8, U5.3
TXO-1: D8.C, TP9.P$1, U7.3, U8.8
TXO-2: D13.C, TP14.P$1, U12.3, U13.8
TXO-3: D18.C, TP19.P$1, U17.3, U18.8
USBVCC: C12.1, C15.+, F2.2, JP12.2, Q1.3
USBVCC1: C24.1, C25.+, F1.2, JP29.2, Q2.3
USBVCC2: C41.1, C42.+, F3.2, JP44.2, Q3.3
USBVCC3: C58.1, C59.+, F4.2, JP59.2, Q4.3
VDD: C2.2, C7.1, C9.1, J1.1, J2.1, J4.2, JP10.5A, JP10.5B, JP10.7A, JP10.7B, JP15.2, R3.2, U1.34, U1.35, U2.5, U4.2, U4.5
VDD1: C14.2, C31.1, C32.1, J8.2, J10.1, J11.1, JP23.5A, JP23.5B, JP23.7A, JP23.7B, JP30.2, R11.2, U8.34, U8.35, U9.5, U10.2, U10.5
VDD2: C35.2, C48.1, C49.1, J14.2, J16.1, J17.1, JP38.5A, JP38.5B, JP38.7A, JP38.7B, JP45.2, R27.2, U13.34, U13.35, U14.5, U15.2, U15.5
VDD3: C52.2, C65.1, C66.1, J20.2, J22.1, J23.1, JP53.5A, JP53.5B, JP53.7A, JP53.7B, JP60.2, R39.2, U18.34, U18.35, U19.5, U20.2, U20.5
VIN: C5.+, D1.C, IC3.3, JP10.1A, JP10.1B
VIN1: C21.+, D6.C, IC1.3, JP23.1A, JP23.1B
VIN2: C38.+, D11.C, IC2.3, JP38.1A, JP38.1B
VIN3: C55.+, D16.C, IC4.3, JP53.1A, JP53.1B
VUSB: C10.1, F2.1, J5.VBUS1, J5.VBUS2, JP12.1, JP14.VBUS
VUSB1: C23.1, F1.1, J9.VBUS1, J9.VBUS2, JP28.VBUS, JP29.1
VUSB2: C40.1, F3.1, J15.VBUS1, J15.VBUS2, JP43.VBUS, JP44.1
VUSB3: C57.1, F4.1, J21.VBUS1, J21.VBUS2, JP58.VBUS, JP59.1
V_BATT: BT1.1, D4.A
V_BATT1: BT2.1, D9.A
V_BATT2: BT3.1, D14.A
V_BATT3: BT4.1, D19.A
~AD0: JP13.1A, JP13.1B, U1.25
~AD1: JP13.2A, JP13.2B, U1.26
~AD2: JP13.3A, JP13.3B, U1.27
~AD3: JP27.1A, JP27.1B, U8.25
~AD3/SWO: J2.6, JP13.4A, JP13.4B, U1.28
~AD3/SWO1: J10.6, JP27.4A, JP27.4B, U8.28
~AD3/SWO2: J16.6, JP42.4A, JP42.4B, U13.28
~AD3/SWO3: J22.6, JP57.4A, JP57.4B, U18.28
~AD4: JP13.5A, JP13.5B, U1.29
~AD5: JP13.6A, JP13.6B, U1.30
~AD6: JP27.2A, JP27.2B, U8.26
~AD7: JP27.3A, JP27.3B, U8.27
~AD8: JP27.5A, JP27.5B, U8.29
~AD9: JP27.6A, JP27.6B, U8.30
~AD10: JP42.1A, JP42.1B, U13.25
~AD11: JP42.2A, JP42.2B, U13.26
~AD12: JP42.3A, JP42.3B, U13.27
~AD13: JP42.5A, JP42.5B, U13.29
~AD14: JP42.6A, JP42.6B, U13.30
~AD15: JP57.1A, JP57.1B, U18.25
~AD16: JP57.2A, JP57.2B, U18.26
~AD17: JP57.3A, JP57.3B, U18.27
~AD18: JP57.5A, JP57.5B, U18.29
~AD19: JP57.6A, JP57.6B, U18.30
~D1: JP26.3A, JP26.3B, U8.2
~D2: JP11.3A, JP11.3B, U1.2
~D3: JP11.4A, JP11.4B, U1.14
~D4: JP26.6A, JP26.6B, U8.15
~D5: JP11.6A, JP11.6B, U1.15
~D6: JP11.7A, JP11.7B, U1.16
~D7: JP11.8A, JP11.8B, U1.17
~D8: JP2.10A, JP2.10B, U1.18
~D9: JP2.9A, JP2.9B, U1.23
~D10: JP2.8A, JP2.8B, U1.24
~D11: JP26.7A, JP26.7B, U8.16
~D12: JP26.8A, JP26.8B, U8.17
~D12/MISO: JP2.6A, JP2.6B, U1.13
~D12/MISO1: JP22.6A, JP22.6B, U8.13
~D12/MISO2: JP37.6A, JP37.6B, U13.13
~D12/MISO3: JP52.6A, JP52.6B, U18.13
~D13: JP22.10A, JP22.10B, U8.18
~D13/SCK: JP2.5A, JP2.5B, R1.1, U1.11
~D13/SCK1: JP22.5A, JP22.5B, R6.1, U8.11
~D13/SCK2: JP37.5A, JP37.5B, R25.1, U13.11
~D13/SCK3: JP52.5A, JP52.5B, R37.1, U18.11
~D14: J6.1, U1.41
~D15: J6.2, U1.42
~D16: J6.3, U1.44
~D17: JP22.9A, JP22.9B, U8.23
~D18: JP22.8A, JP22.8B, U8.24
~D19: J12.1, U8.41
~D20: J12.2, U8.42
~D21: J12.3, U8.44
~D22: JP26.4A, JP26.4B, U8.14
~D23: JP41.3A, JP41.3B, U13.2
~D24: JP41.6A, JP41.6B, U13.15
~D25: JP41.7A, JP41.7B, U13.16
~D26: JP41.8A, JP41.8B, U13.17
~D27: JP37.10A, JP37.10B, U13.18
~D28: JP37.9A, JP37.9B, U13.23
~D29: JP37.8A, JP37.8B, U13.24
~D30: J18.1, U13.41
~D31: J18.2, U13.42
~D32: J18.3, U13.44
~D33: JP41.4A, JP41.4B, U13.14
~D34: JP56.3A, JP56.3B, U18.2
~D35: JP56.6A, JP56.6B, U18.15
~D36: JP56.7A, JP56.7B, U18.16
~D37: JP56.8A, JP56.8B, U18.17
~D38: JP52.10A, JP52.10B, U18.18
~D39: JP52.9A, JP52.9B, U18.23
~D40: JP52.8A, JP52.8B, U18.24
~D41: J24.1, U18.41
~D42: J24.2, U18.42
~D43: J24.3, U18.44
~D44: JP56.4A, JP56.4B, U18.14
~RXI-1: JP11.1A, JP11.1B, U1.19
~RXI-2: JP26.1A, JP26.1B, U8.19
~RXI-3: JP41.1A, JP41.1B, U13.19
~RXI-4: JP56.1A, JP56.1B, U18.19
~SCL: J4.4, JP2.1A, JP2.1B, U1.5
~SCL1: J8.4, JP22.1A, JP22.1B, U8.5
~SCL2: J14.4, JP37.1A, JP37.1B, U13.5
~SCL3: J20.4, JP52.1A, JP52.1B, U18.5
~TXO-1: JP11.2A, JP11.2B, U1.22
~TXO-2: JP26.2A, JP26.2B, U8.22
~TXO-3: JP41.2A, JP41.2B, U13.22
~TXO-4: JP56.2A, JP56.2B, U18.22

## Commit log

2019-04-04 Fix I2C silk. Breakout UART0.
2019-04-15 Rev FP for mics. Add decoupling to mics.
2019-04-16 Update power jack. Change to PDM mics.
2019-04-16 DRC resolved
2019-04-17 Change 10nF to 0.1uF on auto reset circuit
2019-04-17 Change 10nF to 0.1uF on auto-reset circuit
2019-05-10 Version x02 - now uses Artemis v10. One mic, more GPIO, better silk,
2019-05-10 Update silk on Artemis FP
2019-05-17 Adding production panel
2019-05-20 Fixing PWM on pin 7
2019-05-22 Fix pin 33 silk indicator error
2019-05-28 Change labels to match variant.
2019-05-28 Bump version
2019-06-20 Adding ignore. Adding production panel.
2019-07-02 Move testpoint on BlackBoard
